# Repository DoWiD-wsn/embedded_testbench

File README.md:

# Embedded Testbench (ETB)

The **E**mbedded **T**est**b**ench (**ETB**) is a platform consisting of a Raspberry Pi add-on and a Python library designed to enable the testing, analyzing, and profiling of embedded systems.
A focus is laid on low-power embedded systems such as wireless sensor nodes.
Additionally, the ETB supports test automation with the possibility of remote control via TCP/IP.

## Key Facts

* 40-pin expansion header for Raspberry Pi [2|3|4] model B+
* 4 mounting holes matching the Raspberry Pi [2|3|4] model B+ layout
* Compact size of 122 x 56 mm
* 4 controllable voltage domains supplied via own 12V input  
    (0.64 to 5.25V, in 5|10|30|50 mV steps, with a current limit of 3A each; see [MIC24045 datasheet](docs/datasheets/mic24045.pdf))
* 6 wattmeter: one per voltage domain + 2 additional  
    (0 to 26V, +/- 3.2A (max), 1.5 mA resolution, 1% precision; see [INA219 datasheet](docs/datasheets/ina219.pdf))
* 4 channel 16-bit ADC: 2 general + 2 for thermistor (see [ADS1115 datasheet](docs/datasheets/ads1115.pdf))
* I2C multiplexer for easier channel selection (voltage supply + wattmeter; see [TCA9548A datasheet](docs/datasheets/tca9548a.pdf))
* 12-pin expansion header (2x PWM, 6x GPIO, +3V3/+5V, and 2x GND)
* 4 test control signals (reset, enable, running, result)
* Connectors for TWI (2x), OWI (1x), SPI (1x), and UART (1x)
* Connectors for UART (1x) and test control signals (1x)  
    (with MOSFET-based bi-directional level shifter for voltage domain #1)
* Connectors for +3V3, +5V, and GND 
* Dsub 15 HD connector for DUT (e.g., useful for climate chamber experiments)

## Contents

```
.
├── docs                : documents & project documentation
│   └── datasheets      : datasheets of components used
├── kicad               : KiCad files
├── media               : Miscellaneous media (images, etc.)
│   ├── pcb             : Photos and rendered images of the PCB
│   └── schematic       : SVG images of the schematics
└── source              : Python library and example scripts
```

For more information on the PCB (and its design) refer to [docs/pcb_design.md](docs/pcb_design.md).
The python library, its functionality, and usage as well as example scripts are presented in [docs/python_library.md](docs/python_library.md).

## Built with

* [KiCad EAD 5.1.9](https://kicad.org/) - PCB design
* [Python 3.7.3](https://www.python.org/) - Python library

## Contributors

* **Dominik Widhalm** - [***DC-RES***](https://informatics.tuwien.ac.at/doctoral/resilient-embedded-systems/) - [*UAS Technikum Wien*](https://embsys.technikum-wien.at/staff/widhalm/)

Contributions of any kind to improve the project are highly welcome.
For coding bugs or minor improvements simply use pull requests.
However, for major changes or general discussions please contact [Dominik Widhalm](mailto:widhalm@technikum-wien.at?subject=Embedded%20Testbench%20(ETB)%20on%20GitHub).

## Publications

The embedded testbench (ETB) has already been successfully utilized in the following publications:

- Dominik Widhalm, Karl M. Goeschka, and Wolfgang Kastner, "*An open-source wireless sensor node platform with active node-level reliability for monitoring applications*", Sensors 21, no. 22: 7613, 2021, DOI: [10.3390/s21227613](https://doi.org/10.3390/s21227613)
- Dominik Widhalm, Karl M. Goeschka, and Wolfgang Kastner, "*Undervolting on wireless sensor nodes: a critical perspective*", in The 23rd International Conference on Distributed Computing and Networking (ICDCN 2022), January 4-7, 2022, DOI: [10.1145/3491003.3491018](https://doi.org/10.1145/3491003.3491018)
- Dominik Widhalm, Karl M. Goeschka, and Wolfgang Kastner, "*Is Arduino a suitable platform for sensor nodes?*", in The 47th Annual Conference of the IEEE Industrial Electronics Society (IECON 2021), October 13-16, 2021, DOI: [10.1109/IECON48115.2021.9589479](https://doi.org/10.1109/IECON48115.2021.9589479)
- Dominik Widhalm, Karl M. Goeschka, and Wolfgang Kastner, "*Node-level indicators of soft faults in wireless sensor networks*", in The 40th International Symposium on Reliable Distributed Systems (SRDS 2021), September 20-23, 2021, DOI: [10.1109/SRDS53918.2021.00011](https://doi.org/10.1109/SRDS53918.2021.00011)

## Changelog

A list of prior versions and changes between the updates can be found inn the [CHANGELOG.md](CHANGELOG.md) file.
Note that the major and minor number refer to the hardware version of the ETB board while the patch version is used to denote subsequent software versions.

## License

This project is licensed under the MIT License - see the [LICENSE.md](LICENSE.md) file for details.

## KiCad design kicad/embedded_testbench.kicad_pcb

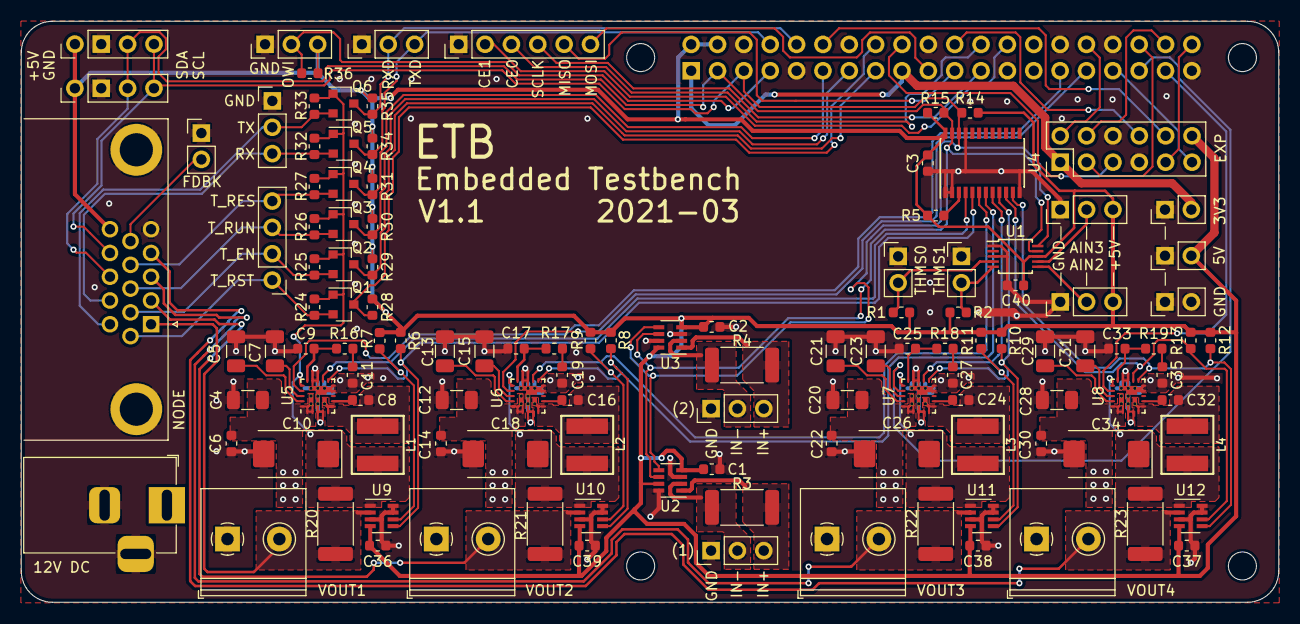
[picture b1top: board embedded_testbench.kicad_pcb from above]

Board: 2 copper layers, 121.2 x 56.0 mm, 127 parts (1 on the bottom side), 86 nets.

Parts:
C1, C2, C3, C6, C8, C14, C16, C22, C24, C30, C32, C36, C37, C38, C39, C40: 100n; C_0603_1608Metric
C4, C12, C20, C28: 22u; C_1206_3216Metric
C5, C7, C13, C15, C21, C23, C29, C31: 2.2u; C_1206_3216Metric
C9, C17, C25, C33: 47p; C_0603_1608Metric
C10, C18, C26, C34: 100u; CP_EIA-7343-31_Kemet-D
C11, C19, C27, C35: 10n; C_0603_1608Metric
J1: 12V INPUT; BarrelJack_Horizontal
J2: THMS1; PinHeader_1x02_P2.54mm_Vertical
J3: THMS2; PinHeader_1x02_P2.54mm_Vertical
J4: VOUT1; TerminalBlock_Philmore_TB132_1x02_P5.00mm_Horizontal
J5: UARTS; PinHeader_1x03_P2.54mm_Vertical
J6: CTRLS; PinHeader_1x04_P2.54mm_Vertical
J7: VOUT2; TerminalBlock_Philmore_TB132_1x02_P5.00mm_Horizontal
J8: VOUT3; TerminalBlock_Philmore_TB132_1x02_P5.00mm_Horizontal
J9: PM1; PinHeader_1x03_P2.54mm_Vertical
J10: VOUT4; TerminalBlock_Philmore_TB132_1x02_P5.00mm_Horizontal
J11: PM2; PinHeader_1x03_P2.54mm_Vertical
J12: SPI; PinHeader_1x06_P2.54mm_Vertical
J13: 5V; PinHeader_1x02_P2.54mm_Vertical
J14: 3V3; PinHeader_1x02_P2.54mm_Vertical
J15: GND; PinHeader_1x02_P2.54mm_Vertical
J16: UART; PinHeader_1x03_P2.54mm_Vertical
J17: OWI; PinHeader_1x03_P2.54mm_Vertical
J18: AIN2; PinHeader_1x03_P2.54mm_Vertical
J19: AIN3; PinHeader_1x03_P2.54mm_Vertical
J20: TWI1; PinHeader_1x04_P2.54mm_Vertical
J21: TWI2; PinHeader_1x04_P2.54mm_Vertical
J22: FDBK; PinHeader_1x02_P2.54mm_Vertical
J23: EXP; PinHeader_2x06_P2.54mm_Vertical
J24: WSN_NODE; DSUB-15-HD_Female_Horizontal_P2.29x1.98mm_EdgePinOffset8.35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
L1, L2, L3, L4: 2.2u; L_Bourns-SRN5040
MK1, MK2, MK3, MK4: M2.5; MountingHole_2.7mm_M2.5
P1: RPi Header; PinSocket_2x20_P2.54mm_Vertical
Q1, Q2, Q3, Q4, Q5, Q6: BSS138; SOT-23
R1, R2: 10k (0.1%); R_0603_1608Metric
R3, R4, R20, R21, R22, R23: 0.1; R_2512_6332Metric
R5, R6, R7, R8, R9, R10, R11, R12, R13, R14, R15, R24, R25, R26, R27, R28, R29, R30, R31, R32, R33, R34, R35, R36: 10k; R_0603_1608Metric
R16, R17, R18, R19: 2.7k; R_0603_1608Metric
U1: ADS1115IDGS; TSSOP-10_3x3mm_P0.5mm
U2, U3, U9, U10, U11, U12: INA219; SOT-23-8
U4: TCA9548APW; TSSOP-24_4.4x7.8mm_P0.65mm
U5, U6, U7, U8: MIC24045; FQFN33-20LD-PL-1

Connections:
+3V3: J14.2, J23.1, P1.1, P1.17
+5V: C1.1, C2.1, C3.1, C36.1, C37.1, C38.1, C39.1, C40.2, J13.2, J17.3, J18.3, J19.3, J20.1, J21.1, J23.12, J24.15, P1.2, P1.4, R1.1, R2.1, R5.2, R6.1, R7.1, R8.1, R9.1, R10.1, R11.1, R12.1, R13.1, R14.1, R15.1, R28.1, R29.1, R30.1, R31.1, R34.1, R35.1, R36.1, U1.8, U2.4, U2.7, U3.4, U3.8, U4.24, U9.4, U10.4, U11.4, U12.4
+12V: C4.1, C6.1, C12.1, C14.1, C20.1, C22.1, C28.1, C30.1, J1.1, U5.1, U5.2, U5.20, U5.21, U6.1, U6.2, U6.20, U6.21, U7.1, U7.2, U7.20, U7.21, U8.1, U8.2, U8.20, U8.21
/AIN0: J2.2, R1.2, U1.4
/AIN1: J3.2, R2.2, U1.5
/AIN2: J18.2, U1.6
/AIN3: J19.2, U1.7
/EN1: P1.29, U5.17
/EN2: P1.31, U6.17
/EN3: P1.35, U7.17
/EN4: P1.37, U8.17
/ENS: J6.2, J24.7, Q2.2, R25.2
/FDBK: J22.2, J24.10
/GPIO16: J23.3, P1.36
/GPIO18: J23.10, P1.12
/GPIO20: J23.4, P1.38
/GPIO21: J23.9, P1.40
/GPIO24: J23.5, P1.18
/GPIO25: J23.8, P1.22
/OWI: J17.2, P1.7, R36.2
/PWM0: J23.2, P1.32
/PWM1: J23.11, P1.33
/RESS: J6.4, J24.9, Q4.2, R27.2
/RSTS: J6.1, J24.6, Q1.2, R24.2
/RUNS: J6.3, J24.8, Q3.2, R26.2
/RXD: J16.2, P1.10, Q6.3, R35.2
/RXS: J5.3, J24.12, Q5.2, R32.2
/SC1: R6.2, U4.5, U5.11, U9.5
/SC2: R8.2, U4.7, U6.11, U10.5
/SC3: R10.2, U4.9, U7.11, U11.5
/SC4: R12.2, U4.11, U8.11, U12.5
/SCL: J20.4, J21.4, J24.14, P1.5, R14.2, U1.10, U2.5, U3.5, U4.22
/SD1: R7.2, U4.4, U5.12, U9.6
/SD2: R9.2, U4.6, U6.12, U10.6
/SD3: R11.2, U4.8, U7.12, U11.6
/SD4: R13.2, U4.10, U8.12, U12.6
/SDA: J20.3, J21.3, J24.13, P1.3, R15.2, U1.9, U2.6, U3.6, U4.23
/SPI_CE0: J12.3, P1.24
/SPI_CE1: J12.2, P1.26
/SPI_MISO: J12.5, P1.21
/SPI_MOSI: J12.6, P1.19
/SPI_SCLK: J12.4, P1.23
/TXD: J16.3, P1.8, Q5.3, R34.2
/TXS: J5.2, J24.11, Q6.2, R33.2
/T_EN: P1.15, Q2.3, R29.2
/T_RES: P1.11, Q4.3, R31.2
/T_RST: P1.16, Q1.3, R28.2
/T_RUN: P1.13, Q3.3, R30.2
/VIN_A1+: J9.3, R3.1, U2.1
/VIN_A1-: J9.2, R3.2, U2.2
/VIN_A2+: J11.3, R4.1, U3.1
/VIN_A2-: J11.2, R4.2, U3.2
/VO1: J4.2, J24.1, R20.2, U9.2
/VO2: J7.2, J24.2, R21.2, U10.2
/VO3: J8.2, J24.3, R22.2, U11.2
/VO4: J10.2, J24.4, R23.2, U12.2
/VOUT1: C10.1, L1.2, Q1.1, Q2.1, Q3.1, Q4.1, Q5.1, Q6.1, R20.1, R24.1, R25.1, R26.1, R27.1, R32.1, R33.1, U5.16, U9.1
/VOUT2: C18.1, L2.2, R21.1, U6.16, U10.1
/VOUT3: C26.1, L3.2, R22.1, U7.16, U11.1
/VOUT4: C34.1, L4.2, R23.1, U8.16, U12.1
GND: C1.2, C2.2, C3.2, C4.2, C5.2, C6.2, C7.1, C9.1, C10.2, C11.1, C12.2, C13.2, C14.2, C15.1, C17.1, C18.2, C19.1, C20.2, C21.2, C22.2, C23.1, C25.1, C26.2, C27.1, C28.2, C29.2, C30.2, C31.1, C33.1, C34.2, C35.1, C36.2, C37.2, C38.2, C39.2, C40.1, J1.2, J1.3, J2.1, J3.1, J4.1, J5.1, J7.1, J8.1, J9.1, J10.1, J11.1, J12.1, J13.1, J14.1, J15.1, J15.2, J16.1, J17.1, J18.1, J19.1, J20.2, J21.2, J22.1, J23.6, J23.7, J24.0, J24.5, P1.6, P1.9, P1.14, P1.20, P1.25, P1.30, P1.34, P1.39, U1.1, U1.3, U2.3, U2.8, U3.3, U3.7, U4.1, U4.2, U4.12, U4.21, U5.3, U5.4, U5.9, U5.10, U5.13, U5.14, U5.22, U6.3, U6.4, U6.9, U6.10, U6.13, U6.14, U6.22, U7.3, U7.4, U7.9, U7.10, U7.13, U7.14, U7.22, U8.3, U8.4, U8.9, U8.10, U8.13, U8.14, U8.22, U9.3, U9.7, U9.8, U10.3, U10.7, U10.8, U11.3, U11.7, U11.8, U12.3, U12.7, U12.8
unnamed: C5.1, U5.19
unnamed: C7.2, U5.18
unnamed: C8.1, U5.7
unnamed: C8.2, L1.1, U5.5, U5.6, U5.23
unnamed: C9.2, R16.2, U5.15
unnamed: C11.2, R16.1
unnamed: C13.1, U6.19
unnamed: C15.2, U6.18
unnamed: C16.1, U6.7
unnamed: C16.2, L2.1, U6.5, U6.6, U6.23
unnamed: C17.2, R17.2, U6.15
unnamed: C19.2, R17.1
unnamed: C21.1, U7.19
unnamed: C23.2, U7.18
unnamed: C24.1, U7.7
unnamed: C24.2, L3.1, U7.5, U7.6, U7.23
unnamed: C25.2, R18.2, U7.15
unnamed: C27.2, R18.1
unnamed: C29.1, U8.19
unnamed: C31.2, U8.18
unnamed: C32.1, U8.7
unnamed: C32.2, L4.1, U8.5, U8.6, U8.23
unnamed: C33.2, R19.2, U8.15
unnamed: C35.2, R19.1
unnamed: R5.1, U4.3

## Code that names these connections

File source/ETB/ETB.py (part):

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
##### GLOBAL VARIABLES #####
# Test control signals
T_RST_GPIO = 23
T_EN_GPIO  = 22
T_RUN_GPIO = 27
T_RES_GPIO = 17


#####
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            # Check if MIC is really enabled
            self._inaaux[i].calibrate()
        # @var __t_rst
        # Object's GPIO pin (BCM) for T_RST (active low)
        self.__trst = T_RST_GPIO
        GPIO.setup(self.__trst, GPIO.OUT)
        GPIO.output(self.__trst, GPIO.HIGH)
        # @var __t_en
        # Object's GPIO pin (BCM) for T_EN
        self.__ten = T_EN_GPIO
        GPIO.setup(self.__ten, GPIO.OUT)
        GPIO.output(self.__ten, GPIO.LOW)
        # @var __t_run
        # Object's GPIO pin (BCM) for T_RUN
        self.__trun = T_RUN_GPIO
        GPIO.setup(self.__trun, GPIO.IN)
        # @var __t_res
        # Object's GPIO pin (BCM) for T_RES
        self.__tres = T_RES_GPIO
        GPIO.setup(self.__tres, GPIO.IN)


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    # Read a T_RUN signal.
    #
    # @param[in]    self            The object pointer.
    # @return       Status of the T_RUN GPIO pin.
    ###
    def trun_read(self):
        # Read GPIO pin
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    # Read a T_RES signal.
    #
    # @param[in]    self            The object pointer.
    # @return       Status of the T_RES GPIO pin.
    ###
    def tres_read(self):
        # Read GPIO pin
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
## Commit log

2021-03-23 Adapted superior gitignore
2021-03-23 Added kicad files of ETB v1.0 (incl. own symbols/footprints)
2021-03-23 Added renderedimage of ETB v1.0 PCB (front/back)
2021-03-23 Added gitignore for kicad projects
2021-03-24 Added preliminary README (docu to be added)
2021-03-24 Added myfootprints as project-specific library
2021-03-24 Removed deprecated parts-to-module assignments file
2021-03-24 Added PCB design documentation
2021-03-24 Updated README (e.g., key facts) Added datasheets
2021-03-24 Updated PCB design docu and added schematics
2021-03-24 Croped schematics and added white background
2021-03-24 Reworked PCB design documentation (table instead of list) Resized PCB board images
2021-03-24 Minor format fix for PCB design documentation
2021-03-24 Minor fix in PCB board (back) image
2021-03-24 Corrected R values in PCB design documentation
2021-03-25 Started with python documentation
2021-03-25 Minor fixes in README
2021-03-29 Renamed documentation directors to docs
2021-03-29 Spell check and markdown formatting
2021-03-30 Started to prepare Python library/sources
2021-03-30 Minor name change for package/module
2021-03-30 Added old files, not ready for use, just for history
2021-03-31 Reworked tc19548 package with doxygen comments (and inside package 'etb' instead of 'testbench')
2021-03-31 Reworked mic24045 package with doxygen comments (inside 'etb')
2021-03-31 Reworked ina219 package with doxygen comments (inside 'etb')
2021-03-31 Reworked core modules and set file right correctly
2021-04-01 INA/MIC/TCA: moved macros from class properties to global variables
2021-04-01 Added minimalistic ADS1115 module
2021-04-01 Reworked core modules to use parameter lists (for value checks)
2021-04-01 Renamed ETB package to uppercase letters
2021-04-01 Removed old etc/core
2021-04-01 Updated setup script
2021-04-01 Added VSM core module (replaces previous ExpSetup)
2021-04-01 Enhanced core INA219 calibration
2021-04-01 Moved datasheets to subdirectories according to the Python module structure
2021-04-01 Cleaned legacy testbench files
2021-04-02 Minor fixed to ETB/core modules
2021-04-02 Reworked and added BME280 sensor module
2021-04-02 Minor format fix in ETB/sens/BME280 module
2021-04-02 Fixed capitalization of variable names in ETB/sens/BME280 module
2021-04-08 Removed stamme library (not needed for ETB)
2021-04-08 Corrected ETB core file access rights
2021-04-08 Added reworkd sensor modules (BME280, DS18B20, LM75; stemma was removed)
2021-04-08 Removed legacy sensor modules
2021-04-08 Removed superfluous init files
2021-04-08 Added placeholder for future communication modules (comm)
2021-04-08 Readded init files (obviously are needed)
2021-04-08 Provided basic package structure
2021-04-08 Added sensor datasheets
2021-04-08 Added JT thermistor datasheet
2021-04-08 Moved JT to sens
2021-04-08 Added JT103 thermistor module
2021-04-08 Reworked ETB/util modules
2021-04-08 Redraw Python dependency graph after source rework
2021-04-08 Updated docs/python_library description (after source rework)
2021-04-08 Added background to Pythond dependency graph ('cause of Github dark mode ...)
2021-04-08 Added ETB package to Python dependency graph
2021-04-14 Added interactive HTML BOM
2021-04-14 Updated schematic, PCB, and BOM (fixed part values and Farnell links)
2021-04-20 Fixed wrong link of 12V DC jack in BOM
2021-04-20 Fixed major PCB issue: wrongly connected 12V DC barrel jack
2021-04-20 First bugfixes after trying on real hardware
2021-04-20 Fixed more bugs and added more module tests for ETB
2021-04-20 Updated PCB design
    Updated silk layer labels
    Some minor improvements
2021-04-21 Bug fixes and improvements for Python library
    Fixed function return values (is not != is False)
    Fixed function headers (doxygen)
    Improved general code quality
2021-04-21 Fixed ADS1115 library (wrong register address)
2021-04-21 More fixes to PCB silk layer
2021-04-29 Cont'd with ETB module and first successful tests
2021-04-29 Extended gitignore with results directory
2021-04-30 Added supply voltage sweep example script
2021-04-30 Added power monitor example script
2021-04-30 Updated python library setup documentation
2021-04-30 Added supply voltage sweep example with result plotting script
2021-04-30 Added ETB self-check example script Fixed some small bugs LM75 suddenly reports wrong value; needs to be checked
2021-07-08 Changed name in license file
2021-08-11 Updated ETB PCB images
2021-08-11 Added missing libraries to voltage sweet demos
2021-09-06 Removed ETB library usage section unintentionally left in python library documentation
2021-09-06 Fixed formatting of python library documentation
2021-09-06 Fixed some more formatting of python library documentation
2021-09-09 Fixed typo in README
2021-09-29 Started implementing SHTC3 library (not working yet because of 16-bit register addresses)
2021-10-06 Fixed incorrect (absolute) path for kicad symbol library (need to find a relative solution)
2021-10-25 Added wake-up delay to SHTC3 sleep_disable method
2021-10-27 Added test control signal handling to ETB module
2021-11-18 Added related publications (i.e., where the ETB was successfully used)
2021-11-18 Changed license file extension to markdown
2021-11-18 Added changelog for future extensions/improvements
2021-11-18 Fixed typo in license file name
2021-11-20 Added IECON paper DOI
2021-11-20 Added note on publications
2022-02-04 Updated PCB plots (incl. 3D view)
2022-02-04 Fixed missing file ending in README
2022-02-28 Added missing 3d models and updated figures
2022-02-28 Remoded unintended artefacts from PCB figures
2022-05-20 Fixed typo in ICDCN DOI
2022-12-15 Fix missing tab in makefile
